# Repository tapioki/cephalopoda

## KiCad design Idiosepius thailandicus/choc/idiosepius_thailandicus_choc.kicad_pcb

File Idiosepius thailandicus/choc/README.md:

# Idiosepius thailandicus

AKA I. thailandicus, I.T., "The sixth one", "Pygmy bobtail squid"

Designed with the ARTSEY layout in mind, but could also be used with ASTENIOP.
BlueMicro compatible.

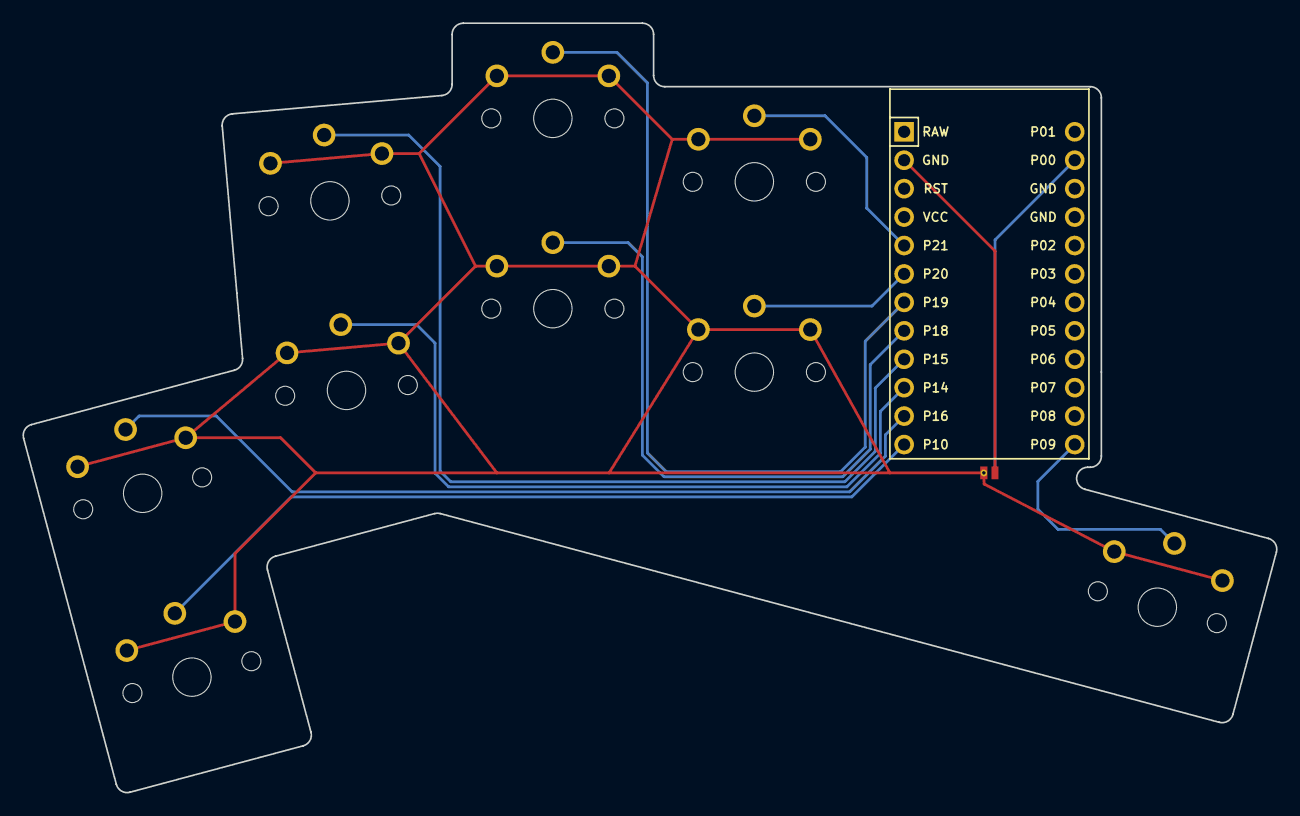
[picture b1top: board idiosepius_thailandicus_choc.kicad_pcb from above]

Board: 2 copper layers, 112.0 x 68.7 mm, 12 parts (0 on the bottom side), 11 nets.

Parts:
C1: ProMicro
J1, J2: Jumper
S1, S2, S3, S4, S5, S6, S7, S8, S9: PG1350

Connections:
GND: C1.2, C1.15, C1.16, J1.1, J1.2, J2.1, S1.1, S2.1, S3.1, S4.1, S5.1, S6.1, S7.1, S8.1, S9.1
P0: C1.14, J2.2
P9: C1.24, S9.2
P10: C1.12, S1.2
P14: C1.10, S3.2
P15: C1.9, S4.2
P16: C1.11, S2.2
P18: C1.8, S5.2
P19: C1.7, S6.2
P20: C1.6, S7.2
P21: C1.5, S8.2

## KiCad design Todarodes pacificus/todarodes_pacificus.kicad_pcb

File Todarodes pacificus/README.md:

# Todarodes pacificus

AKA T. pacificus, T.P., "The fourth one", "Japanese flying squid"

30 keys, 15, 5, 0, -5, -5 degree splay. My take on the Hummingbird layout.

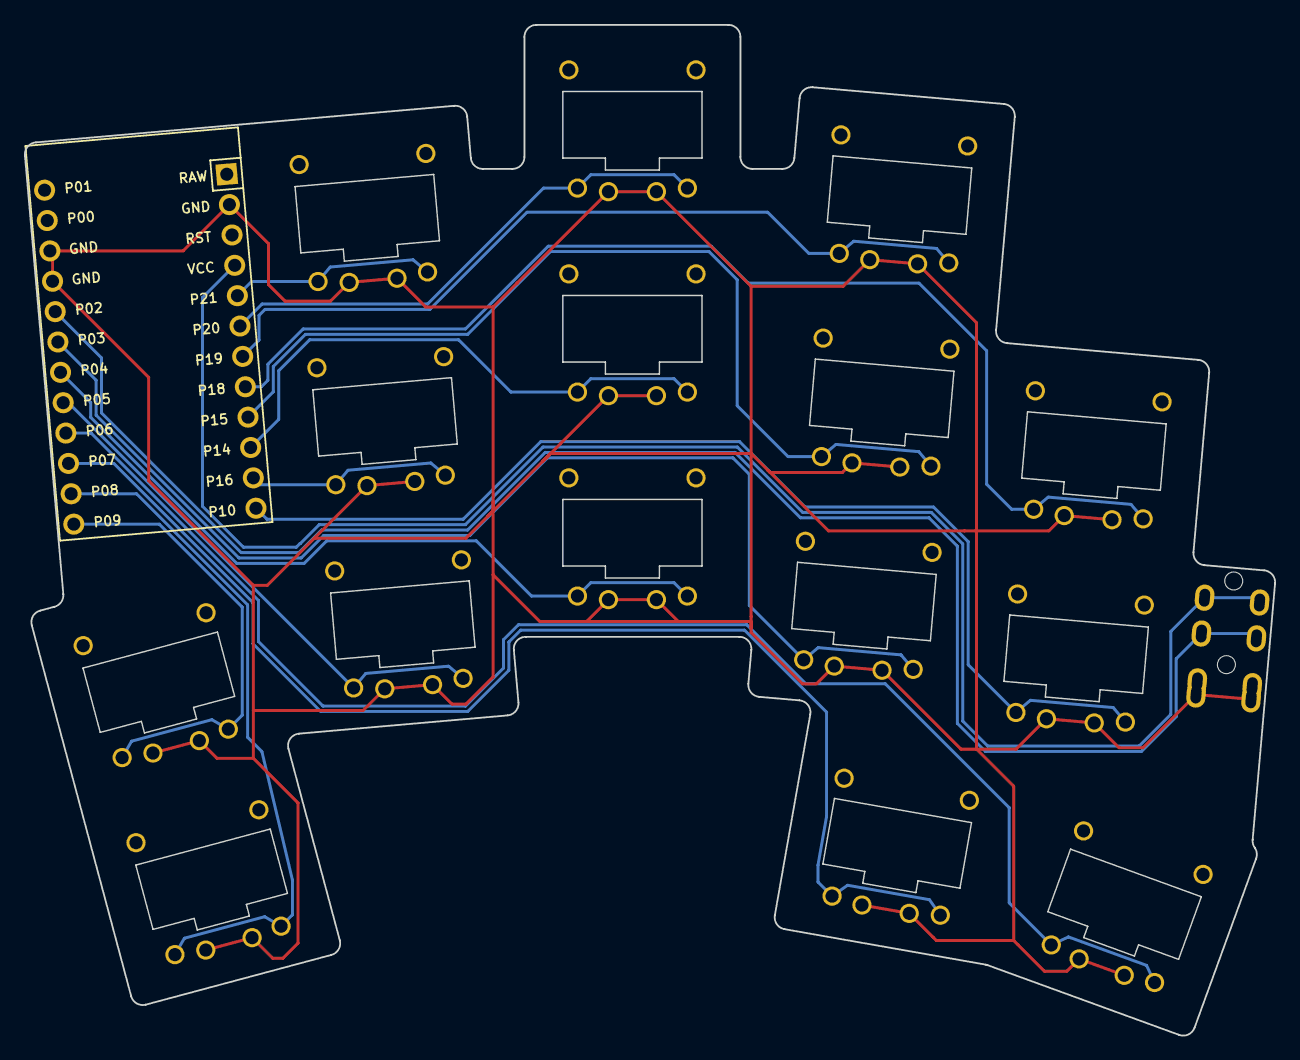
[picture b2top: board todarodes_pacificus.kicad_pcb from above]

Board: 2 copper layers, 104.2 x 84.2 mm, 16 parts (0 on the bottom side), 16 nets.

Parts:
C1: ProMicro
S1, S2, S3, S4, S5, S6, S7, S8, S9, S10, S11, S12, S13, S14, S15: Kailh_PG1232

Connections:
GND: C1.2, C1.15, C1.16, S1.2, S2.2, S3.2, S4.2, S5.2, S6.2, S7.2, S8.2, S9.2, S10.2, S11.2, S12.2, S13.2, S14.2, S15.2
P3: C1.18, S9.1
P4: C1.19, S6.1
P5: C1.20, S3.1
P6: C1.21, S15.1
P7: C1.22, S14.1
P8: C1.23, S1.1
P9: C1.24, S2.1
P10: C1.12, S12.1
P14: C1.10, S7.1
P15: C1.9, S10.1
P16: C1.11, S4.1
P18: C1.8, S13.1
P19: C1.7, S11.1
P20: C1.6, S8.1
P21: C1.5, S5.1
